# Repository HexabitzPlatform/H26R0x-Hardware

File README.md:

# H26R0x-Hardware
Hexabitz Load Cell Sensor Module Hardware Design

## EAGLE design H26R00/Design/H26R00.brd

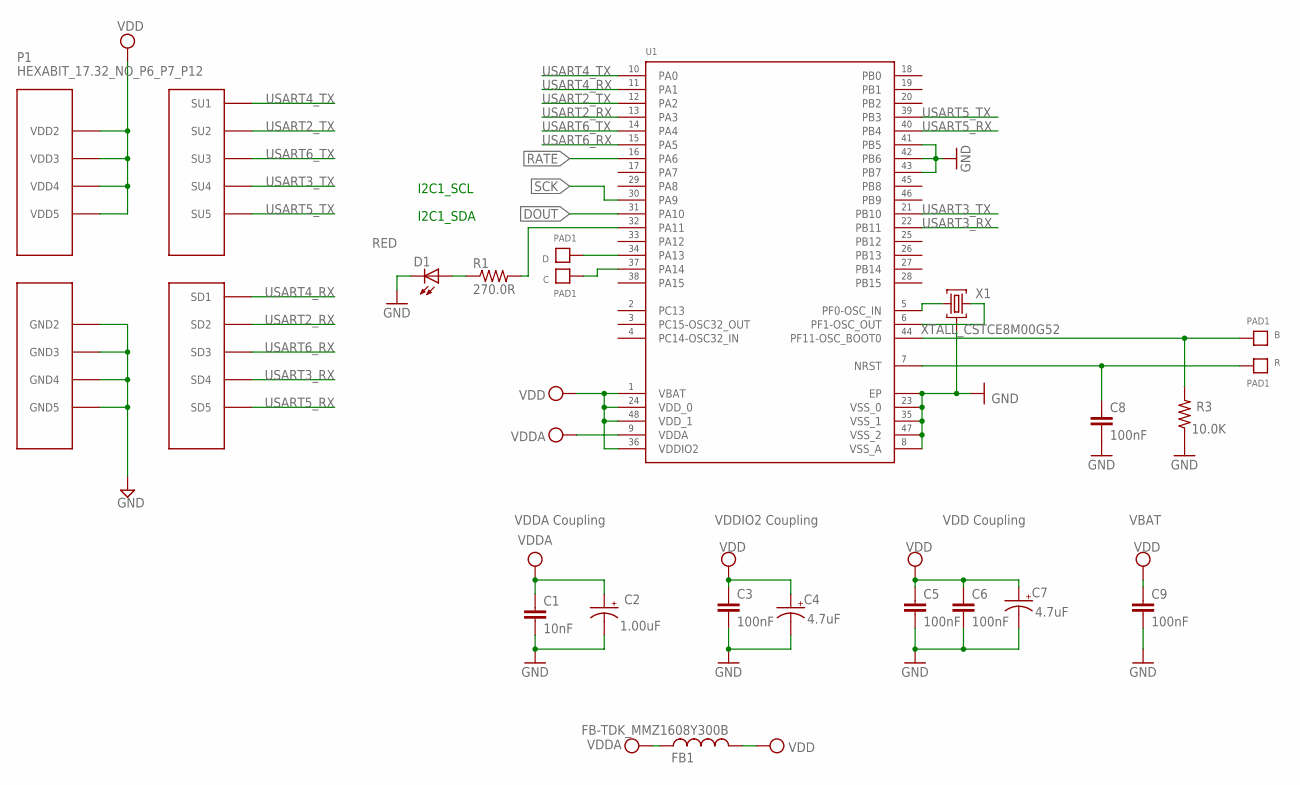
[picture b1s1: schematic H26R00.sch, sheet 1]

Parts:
B: PAD1
C: PAD1
C1: 10nF; C-0603; TOLERANCE 10%; VOLTAGE_RATING 50V; MPN C0603C103K5RACTU
C2: 1.00uF; C-0805-POL; TOLERANCE 10%; VOLTAGE_RATING 16V; MPN CC0805KKX7R7BB105
C3, C6, C8: 100nF; C-0603; TOLERANCE 10%; VOLTAGE_RATING 10V; MPN C0603C104K8RACTU
C4, C7: 4.7uF; C-0805-POL; TOLERANCE 10%; VOLTAGE_RATING 25V; MPN GRM21BC81E475KA12L
C5: 100nF; C-0603; TOLERANCE 10%; VOLTAGE_RATING 10; MPN C0603C104K8RACTU
C9: 100nF; C-0603; TOLERANCE 10V; VOLTAGE_RATING 10%; MPN C0603C104K8RACTU
D: PAD1
D1: RED; VLMS1300-GS08; MPN VLMS1300-GS08
FB1: FB-TDK_MMZ1608Y300B; MPN MMZ1608Y300B
P1: HEXABIT_17.32_NO_P6_P7_P12
R: PAD1
R1: 270.0R; R-0603; TOLERANCE 1%; MPN RC0603FR-07270RL
R3: 10.0K; R-0603; TOLERANCE 5%; MPN RC0603JR-0710KL
U1: STM32F091CBU6
X1: XTALL_CSTCE8M00G52

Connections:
B1: B.P$1, B.P$2, R3.2, U1.P$44 (PF11-OSC_BOOT0)
DOUT: U1.P$31 (PA10); also elsewhere on the board
GND: C1.2, C2.2 (-), C3.2, C4.2 (-), C5.2, C6.2, C7.2 (-), C8.2, C9.2, D1.C, P1.PAD_PD8 (GND2), P1.PAD_PD9 (GND3), P1.PAD_PD10 (GND4), P1.PAD_PD11 (GND5), R3.1, U1.EP, U1.P$8 (VSS_A), U1.P$23 (VSS_0), U1.P$35 (VSS_1), U1.P$41 (PB5), U1.P$42 (PB6), U1.P$43 (PB7), U1.P$47 (VSS_2), X1.P$2 (2); also elsewhere on the board
unnamed: R1.2, U1.P$32 (PA11)
unnamed: D1.A, R1.1
unnamed: U1.P$5 (PF0-OSC_IN), X1.P$1 (1)
unnamed: U1.P$6 (PF1-OSC_OUT), X1.P$3 (3)
unnamed: D.P$1, D.P$2, U1.P$34 (PA13)
unnamed: C.P$1, C.P$2, U1.P$37 (PA14)
R1: C8.1, R.P$1, R.P$2, U1.P$7 (NRST)
RATE: U1.P$16 (PA6); also elsewhere on the board
SCK: U1.P$30 (PA9); also elsewhere on the board
USART2_RX: P1.PAD_PD2 (SD2), U1.P$13 (PA3)
USART2_TX: P1.PAD_PU2 (SU2), U1.P$12 (PA2)
USART3_RX: P1.PAD_PD4 (SD4), U1.P$22 (PB11)
USART3_TX: P1.PAD_PU4 (SU4), U1.P$21 (PB10)
USART4_RX: P1.PAD_PD1 (SD1), U1.P$11 (PA1)
USART4_TX: P1.PAD_PU1 (SU1), U1.P$10 (PA0)
USART5_RX: P1.PAD_PD5 (SD5), U1.P$40 (PB4)
USART5_TX: P1.PAD_PU5 (SU5), U1.P$39 (PB3)
USART6_RX: P1.PAD_PD3 (SD3), U1.P$15 (PA5)
USART6_TX: P1.PAD_PU3 (SU3), U1.P$14 (PA4)
VDD: C3.1, C4.1 (+), C5.1, C6.1, C7.1 (+), C9.1, FB1.2, P1.PAD_PU8 (VDD2), P1.PAD_PU9 (VDD3), P1.PAD_PU10 (VDD4), P1.PAD_PU11 (VDD5), U1.P$1 (VBAT), U1.P$24 (VDD_0), U1.P$36 (VDDIO2), U1.P$48 (VDD_1); also elsewhere on the board
VDDA: C1.1, C2.1 (+), FB1.1, U1.P$9 (VDDA)

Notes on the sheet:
VDDA Coupling
VDDIO2 Coupling
VDD Coupling
VBAT
I2C1_SCL
I2C1_SDA

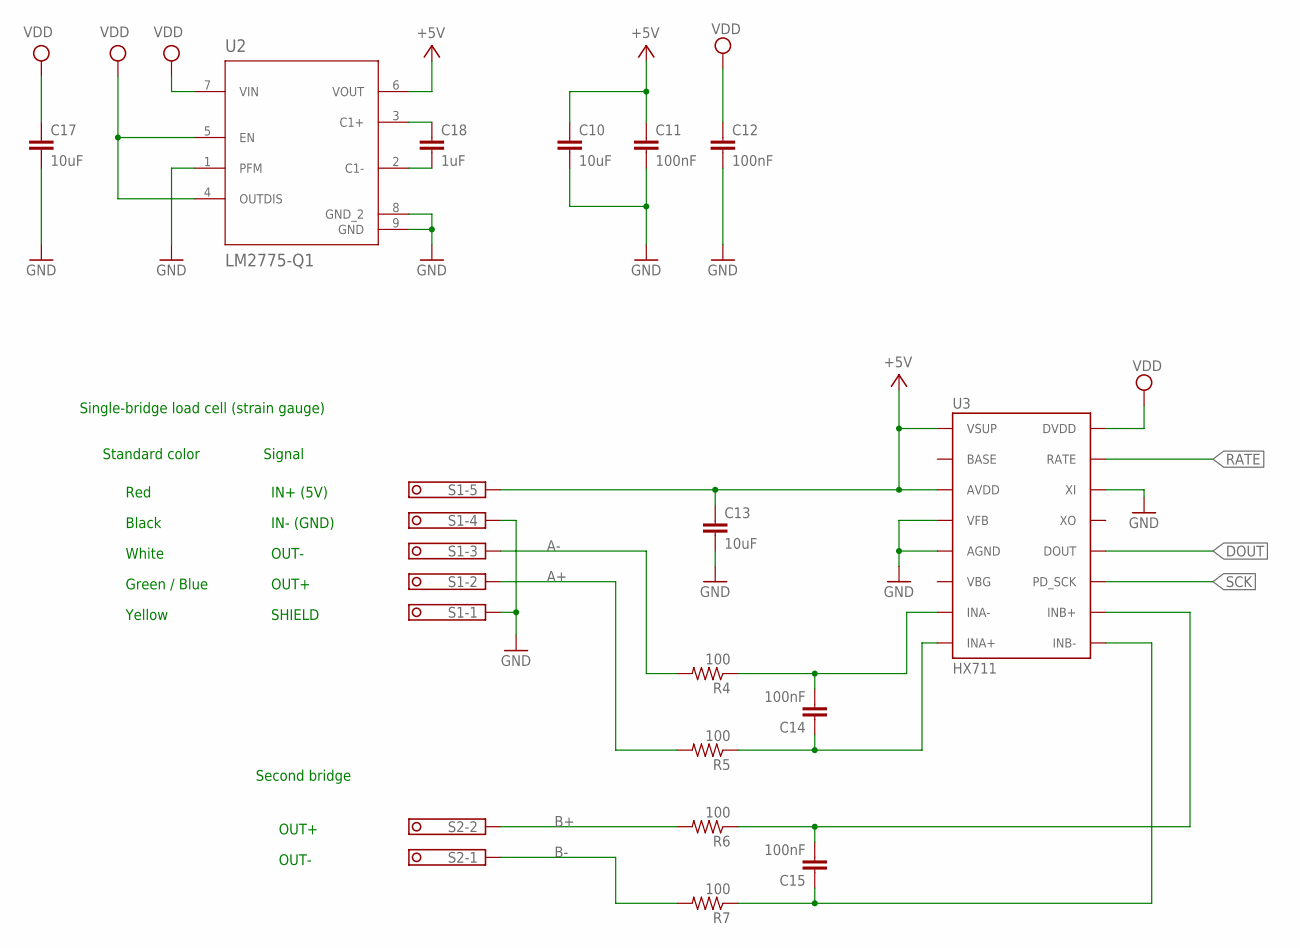
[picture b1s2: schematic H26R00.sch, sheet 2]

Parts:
C10, C13, C17: 10uF; C-0603; TOLERANCE 10%; VOLTAGE_RATING 10V; MPN GRM188R61A106KE69D
C11, C12: 100nF; C-0603; TOLERANCE 10%; VOLTAGE_RATING 10V; MPN C0603C104K8RACTU
C14, C15: 100nF; C-0603; TOLERANCE 10V; VOLTAGE_RATING 10%; MPN C0603C104K8RACTU
C18: 1uF; C-0603; TOLERANCE 10%; VOLTAGE_RATING 10V; MPN GRM188R61A105KA61J
R4, R5, R6, R7: 100; R-0603; TOLERANCE 5%; MPN RC0603JR-07100RL
S1: CON-PHOENIX-350_1751277; MPN 1984646
S2: CON-PHOENIX-350_1751248; MPN 1984617
U2: LM2775-Q1; DSG0008A
U3: HX711; HX711_SO16; MPN HX711

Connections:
+5V: C10.1, C11.1, C13.1, S1.5, U2.6 (VOUT), U3.1 (VSUP), U3.3 (AVDD)
A+: R5.2, S1.2
A-: R4.2, S1.3
B+: R6.2, S2.2
B-: R7.2, S2.1
DOUT: U3.12 (DOUT); also elsewhere on the board
GND: C10.2, C11.2, C12.2, C13.2, C17.2, S1.1, S1.4, U2.1 (PFM), U2.8 (GND_2), U2.9 (GND), U3.4 (VFB), U3.5 (AGND), U3.14 (XI); also elsewhere on the board
INA+: C14.1, R5.1, U3.8 (INA+)
INA-: C14.2, R4.1, U3.7 (INA-)
INB+: C15.2, R6.1, U3.10 (INB+)
INB-: C15.1, R7.1, U3.9 (INB-)
unnamed: C18.1, U2.3 (C1+)
unnamed: C18.2, U2.2 (C1-)
RATE: U3.15 (RATE); also elsewhere on the board
SCK: U3.11 (PD_SCK); also elsewhere on the board
VDD: C12.1, C17.1, U2.4 (OUTDIS), U2.5 (EN), U2.7 (VIN), U3.16 (DVDD); also elsewhere on the board

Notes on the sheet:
Standard color
Red
Black
White
Green / Blue
Yellow
Single-bridge load cell (strain gauge)
IN+ (5V)
IN- (GND)
OUT-
OUT+
SHIELD
Signal
Second bridge

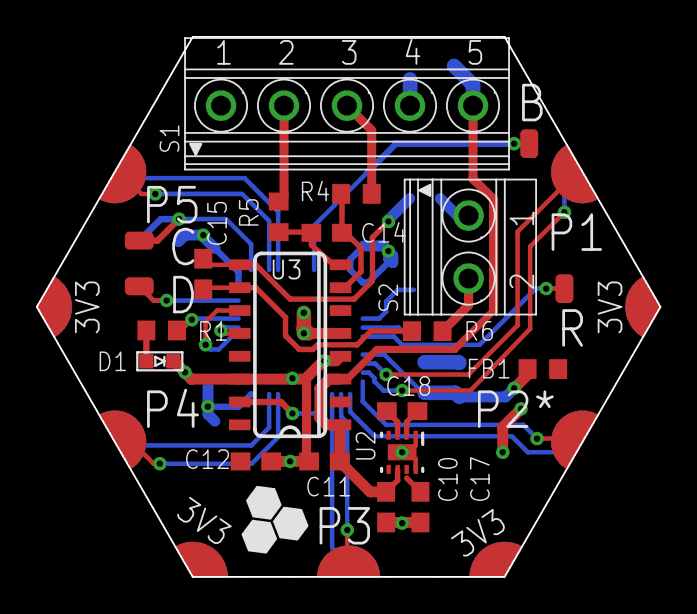
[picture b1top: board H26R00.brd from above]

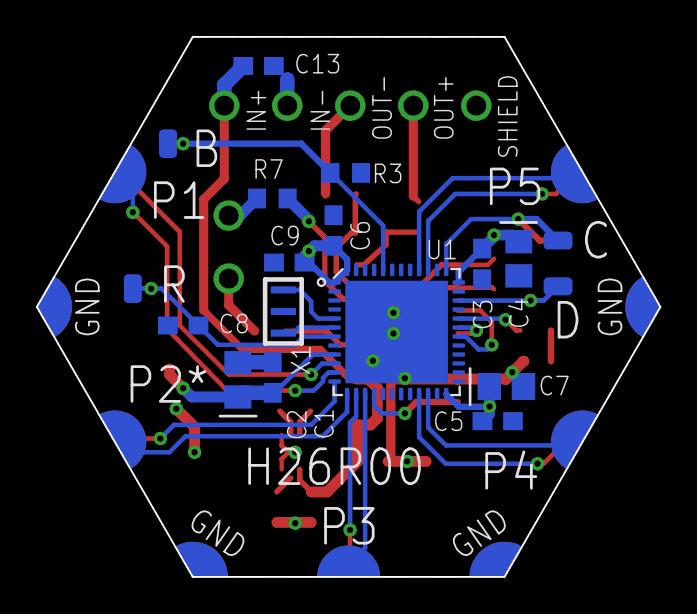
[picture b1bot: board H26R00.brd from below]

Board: 2 copper layers, 34.6 x 30.0 mm, 36 parts (14 on the bottom side), 35 nets.

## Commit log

2019-05-23 First release rev 0
2019-06-30 Update schematics PDF with correct colors
2020-02-10 Adding 3.3V to 5V converter to power the bridge Power the HX711 and bridge from 5V and don't use HX711 regulator
2020-02-10 Update schematics, gerber, drill, pick n place files
2020-02-10 Update BOM Release V0
2023-09-26 - Change the MCU to stm32g0b1ceu6n - Improve the layout design for better performance - Edit the terminal block connectors naming in sch and pcb
2024-10-01 Fix folder arrangement.
